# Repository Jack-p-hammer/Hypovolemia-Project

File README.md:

# Hypovolemia Project

KiCad PCB project for the Hypovolemia Project.

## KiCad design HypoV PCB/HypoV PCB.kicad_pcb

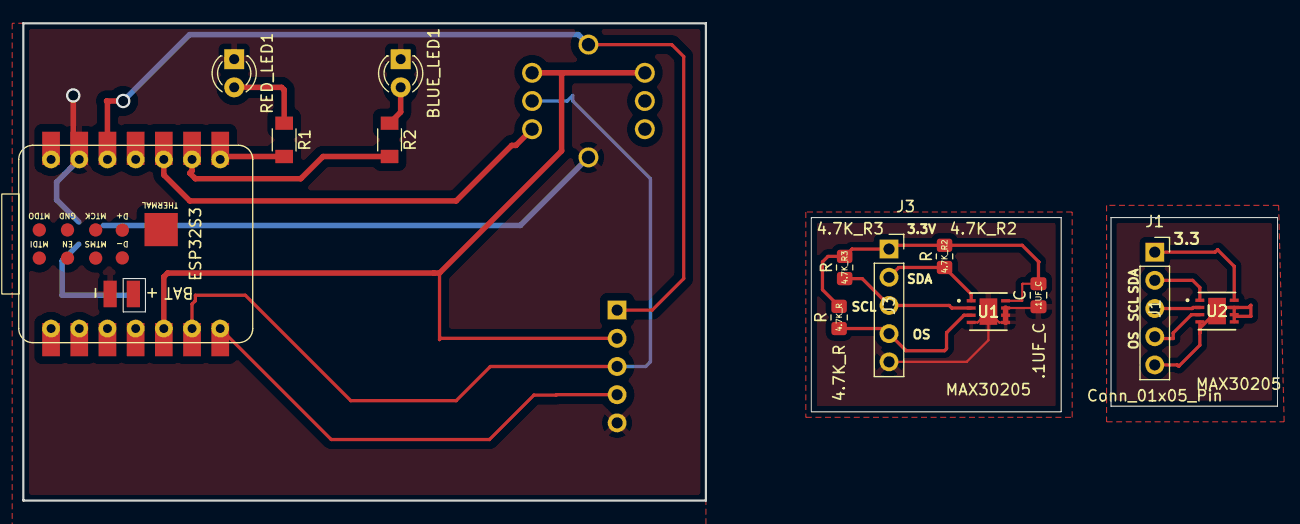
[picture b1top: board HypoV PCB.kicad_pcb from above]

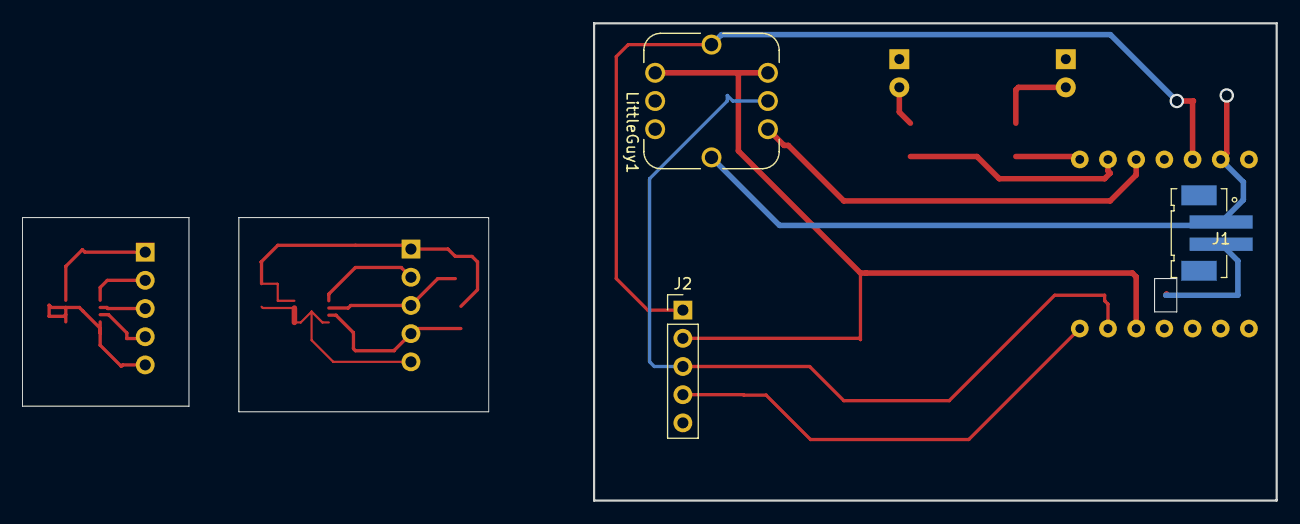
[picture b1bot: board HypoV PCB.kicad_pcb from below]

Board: 2 copper layers, 113.0 x 43.0 mm, 16 parts (3 on the bottom side), 20 nets.

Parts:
4.7K_R, 4.7K_R2, 4.7K_R3: R; R_0805_2012Metric_Pad1.20x1.40mm_HandSolder
.1UF_C: C; C_0805_2012Metric_Pad1.18x1.45mm_HandSolder
BLUE_LED1: LED; LED_D3.0mm
ESP32S3: 113991054; SeeedStudio_XIAO_ESP32S3
J1, J3: Conn_01x05_Pin; PinSocket_1x05_P2.54mm_Vertical
J1#2: Conn_Header_JST_PH_1x02_P2mm_Vertical_SMD; Header_JST_PH_1x02_P2mm_Vertical_SMD
J2: Conn_01x05_Pin; PinHeader_1x05_P2.54mm_Vertical
LittleGuy1: MAXREFDES117_; MODULE_MAXREFDES117_
R1, R2: R; R_1206
RED_LED1: LED; LED_D3.0mm
U1, U2: MAX30205; 21-0137_T833&plus_2_MXM-M

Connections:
+3.3V: ESP32S3.12 (3V3), J2.1, LittleGuy1.VIN
+3V3: 4.7K_R.1, 4.7K_R2.1, 4.7K_R3.1, .1UF_C.1, J3.1, U1.8 (VDD)
+3V32: J1.1, U2.8 (VDD)
/D9: ESP32S3.10 (D9), LittleGuy1.INT
/OS: ESP32S3.7 (D6), J2.4
/SCL: ESP32S3.6 (D5), J2.3, LittleGuy1.SCL1 (SCL__1)
/SDA: ESP32S3.5 (D4), J2.2, LittleGuy1.SDA, LittleGuy1.SDA1 (SDA__1)
GND: .1UF_C.2, BLUE_LED1.1 (K), ESP32S3.13 (GND), ESP32S3.15 (BAT_GND), J1#2.1, J2.5, J3.5, LittleGuy1.GND, RED_LED1.1 (K), U1.4 (GND), U1.5 (A2), U1.6 (A1), U1.7 (A0), U1.9 (EPAD)
GND2: J1.5, U2.4 (GND), U2.5 (A2), U2.6 (A1), U2.7 (A0), U2.9 (EPAD)
unnamed: BLUE_LED1.2 (A), R2.1
unnamed: ESP32S3.16 (BAT_VIN), J1#2.2
unnamed: ESP32S3.8 (D7), R1.2
unnamed: ESP32S3.9 (D8), R2.2
unnamed: J1.2, U2.1 (SDA)
unnamed: J1.3, U2.2 (SCL)
unnamed: J1.4, U2.3 (OS)
unnamed: 4.7K_R2.2, J3.2, U1.1 (SDA)
unnamed: 4.7K_R3.2, J3.3, U1.2 (SCL)
unnamed: 4.7K_R.2, J3.4, U1.3 (OS)
unnamed: R1.1, RED_LED1.2 (A)

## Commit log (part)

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2026-04-27 Initial commit: add README
2026-04-27 Add HypoV PCB project files
2026-04-27 adding code, cad, and joy
2026-04-27 started wiring up temp sensor according to datasheet
2026-04-28 more edits
2026-04-28 added pcb
2026-04-29 added final pcb stuff
2026-04-29 added my extra files and stuff?
2026-05-01 LED file
2026-05-01 CAD changes
2026-05-01 added the breakout board
2026-05-01 added the led code
2026-05-03 wireless comms working, firmware files for neck and arm sensor created
2026-05-03 re-formatted the dashboard organization
2026-05-03 forearm with PPG sensor working
2026-05-03 added code for temp sensor data and printout
2026-05-04 added temp sensor sender code
2026-05-04 added temp sensor receiver and diff code
2026-05-04 changed to absolute value of temperature differential
2026-05-04 added final pcb
2026-05-04 added basic temp reading sketch and the pcb
2026-05-06 holy heck stuff works
2026-05-10 little guy added
2026-05-10 hypovolemia platform io project
